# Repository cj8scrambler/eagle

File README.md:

Eagle Repository
=======

This is a repository to keep track of various hardware projects.

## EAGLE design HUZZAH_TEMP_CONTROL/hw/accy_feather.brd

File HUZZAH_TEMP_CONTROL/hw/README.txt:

To generate gerber files for OSH park:
  1) open schematic in Eagle
  2) Run the “CAM Processor”
  3) Select File -> CAM Processor
  4) Choose the OSHPark_eagle[version].cam that corresponds to your version of Eagle PCB
  5) Run 'Process Job'
  6) zip oshpark_gerbers.zip *.ger *.xln
  7) Upload oshpark_gerbers.zip to OSHPark

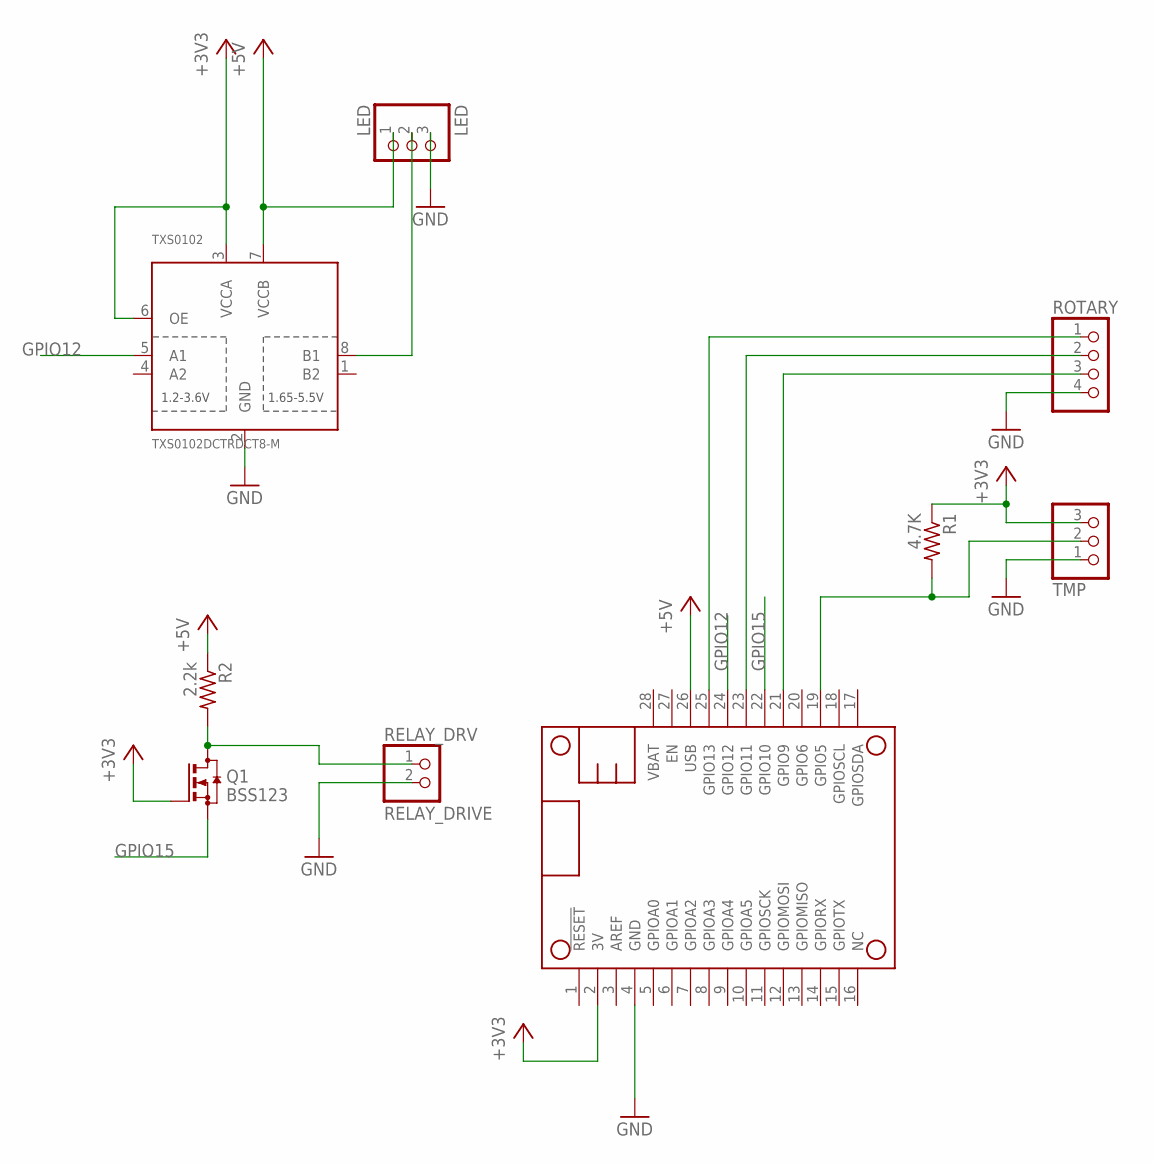
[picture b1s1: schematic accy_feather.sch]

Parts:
LED: LED; 1X03-CLEANBIG
MS1: FEATHERWING
Q1: BSS123; SOT23
R1: 4.7K; R0603
R2: 2.2k; R0603
RELAY_DRV: RELAY_DRIVE; 1X02
ROTARY: PINHD-1X4; 1X04
TMP: PINHD-1X3CB; 1X03-CLEANBIG
TXS0102: TXS0102DCTRDCT8-M; DCT8-M

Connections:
+3V3: MS1.2 (3V), Q1.1 (G), R1.1, TMP.3, TXS0102.3 (VCCA), TXS0102.6 (OE)
+5V: LED.1, MS1.26 (USB), R2.1, TXS0102.7 (VCCB)
BTN: MS1.21 (GPIO9), ROTARY.3
GND: LED.3, MS1.4 (GND), RELAY_DRV.2, ROTARY.4, TMP.1, TXS0102.2 (GND)
GPIO12: MS1.24 (GPIO12), TXS0102.5 (A1)
GPIO15: MS1.22 (GPIO10), Q1.2 (S)
LED_DATA: LED.2, TXS0102.8 (B1)
unnamed: Q1.3 (D), R2.2, RELAY_DRV.1
ROT1: MS1.25 (GPIO13), ROTARY.1
ROT2: MS1.23 (GPIO11), ROTARY.2
TMP_DATA: MS1.19 (GPIO5), R1.2, TMP.2

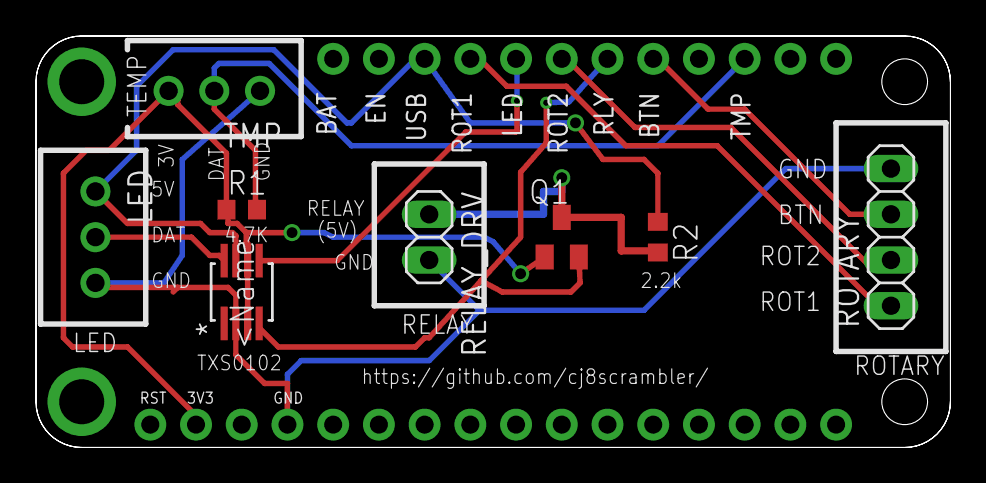
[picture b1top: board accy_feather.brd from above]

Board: 2 copper layers, 50.8 x 22.9 mm, 9 parts (0 on the bottom side), 11 nets.

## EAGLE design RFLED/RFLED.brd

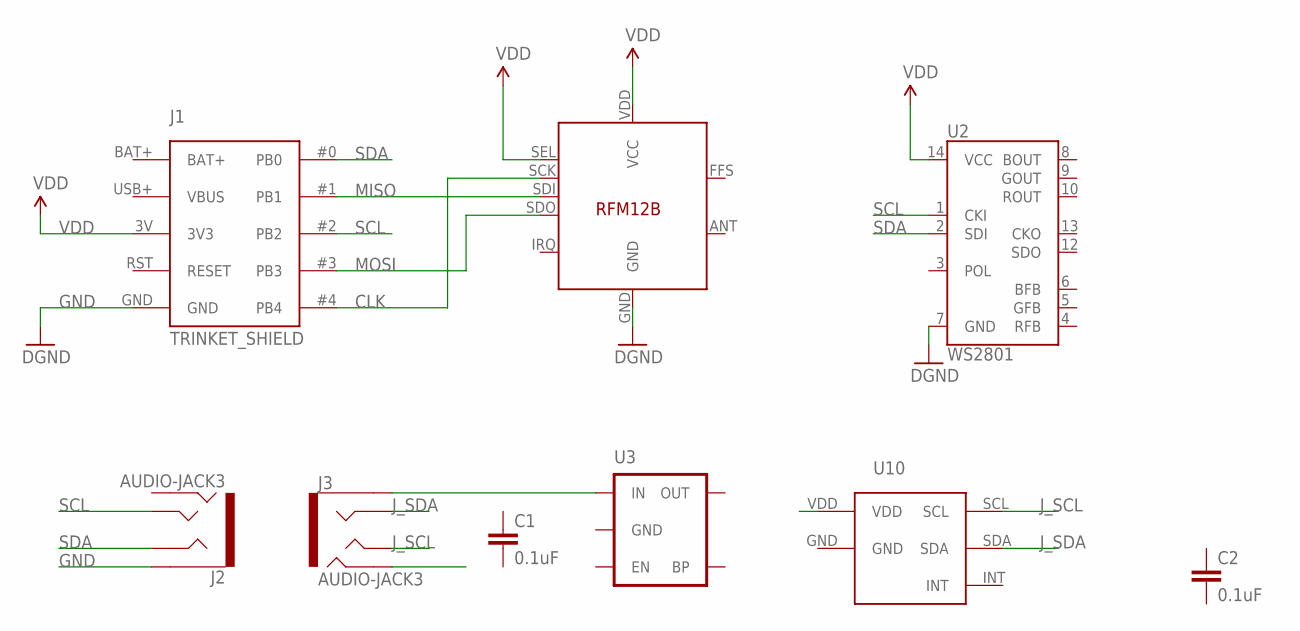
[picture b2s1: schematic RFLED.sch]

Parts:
C1, C2: 0.1uF; 0603-CAP
J1: TRINKET_SHIELD
J2, J3: AUDIO-JACK3; AUDIO-JACK-TRRS-SMD
U1: RFM12B
U2: WS2801; SOP-14
U3: MIC52053.3V; SOT23-5
U10: TC3472DFNL6_WIDE; DFNL6_WIDE

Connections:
BAT+: J1.BAT+
CLK: J1.#4 (PB4), U1.SCK
GND: J1.GND, J2.EARTH, U1.GND, U2.7 (GND)
J_SCL: J3.TIP, U10.SCL
J_SDA: J3.RING1, U10.SDA
J_VDD: J3.RING2
MISO: J1.#1 (PB1), U1.SDI
MOSI: J1.#3 (PB3), U1.SDO
unnamed: J3.EARTH, U3.1 (IN)
SCL: J1.#2 (PB2), J2.TIP, U2.1 (CKI)
SDA: J1.#0 (PB0), J2.RING1, U2.2 (SDI)
VBUS: J1.USB+ (VBUS)
VDD: J1.3V (3V3), U1.SEL, U1.VDD (VCC), U2.14 (VCC)

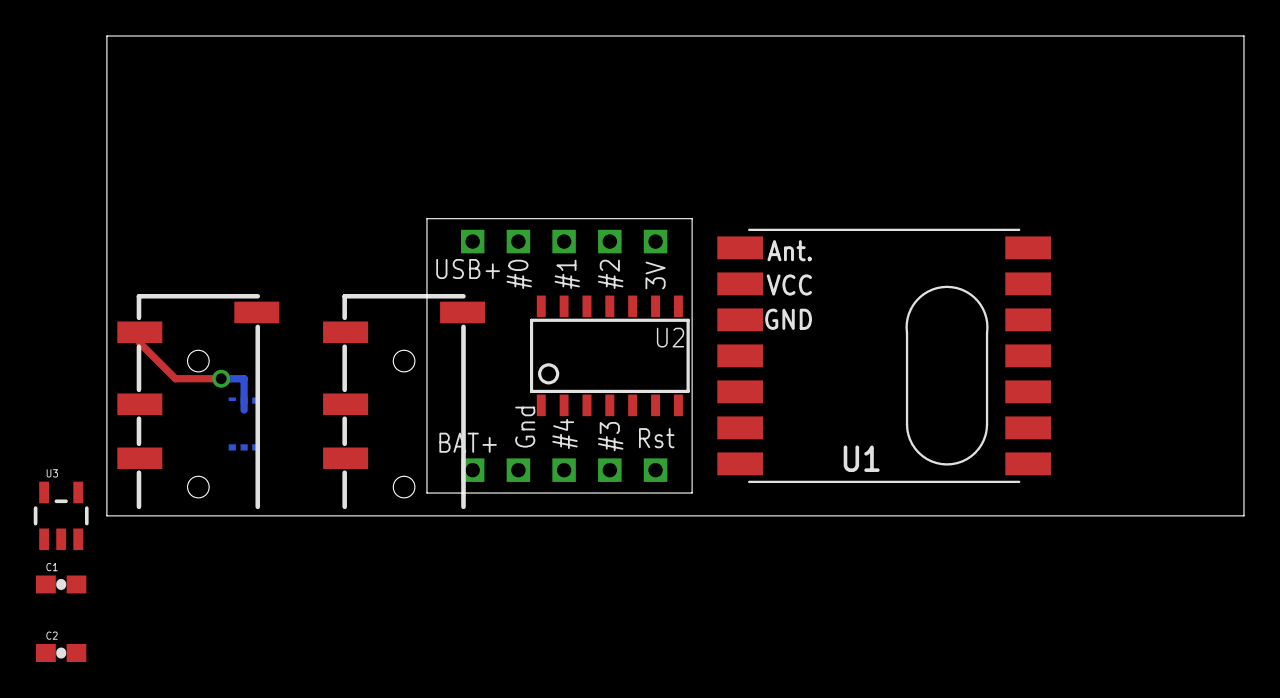
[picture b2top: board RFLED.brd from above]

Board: 2 copper layers, 63.2 x 26.7 mm, 9 parts (1 on the bottom side), 10 nets.

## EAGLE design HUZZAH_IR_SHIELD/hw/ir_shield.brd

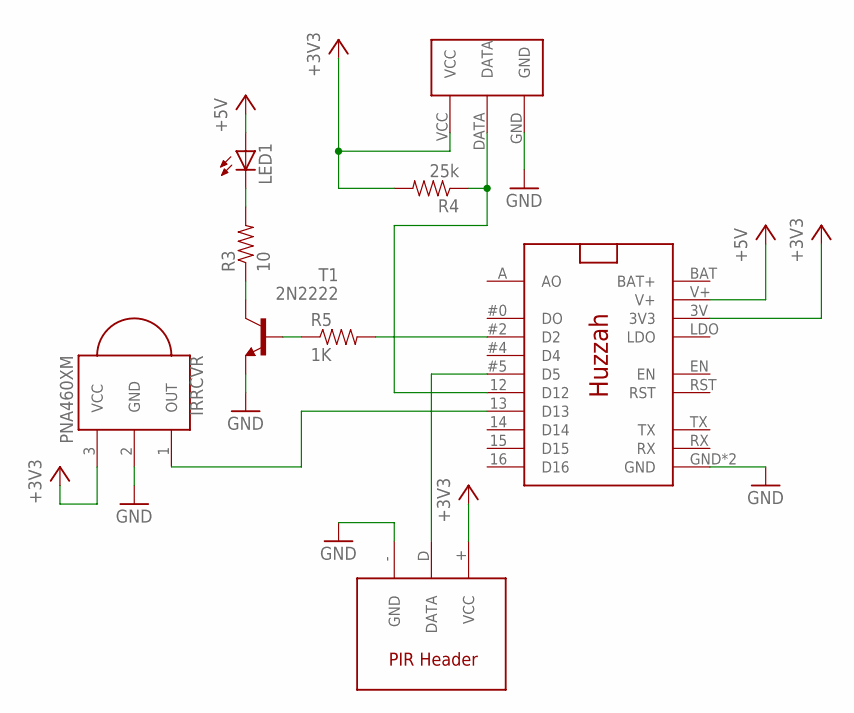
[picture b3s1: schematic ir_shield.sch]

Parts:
IRRCVR: PNA460XM
LED1: LEDIRL80A; IRL80A
R3: 10; 0402-RES
R4: 25k; 0402-RES
R5: 1K; 0402-RES
T1: 2N2222; TO92-EBC-OVAL
U$1: HUZZAH_SHIELDOUTSIDE; HUZZAH_OUTSIDE
U$3: DHT11VERT; DHT11-VERT
U$4: PIR; 3_PIN_HEADER

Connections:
+3V3: IRRCVR.3 (VCC), R4.2, U$1.3V (3V3), U$3.VCC, U$4.+ (VCC)
+5V: LED1.A, U$1.V+
GND: IRRCVR.2 (GND), T1.E, U$1.GND, U$1.GND2 (GND), U$3.GND, U$4.- (GND)
unnamed: LED1.K (C), R3.2
unnamed: R3.1, T1.C
unnamed: R5.1, T1.B
unnamed: R5.2, U$1.#2 (D2)
unnamed: IRRCVR.1 (OUT), U$1.13 (D13)
unnamed: R4.1, U$1.12 (D12), U$3.DATA
unnamed: U$1.#5 (D5), U$4.D (DATA)

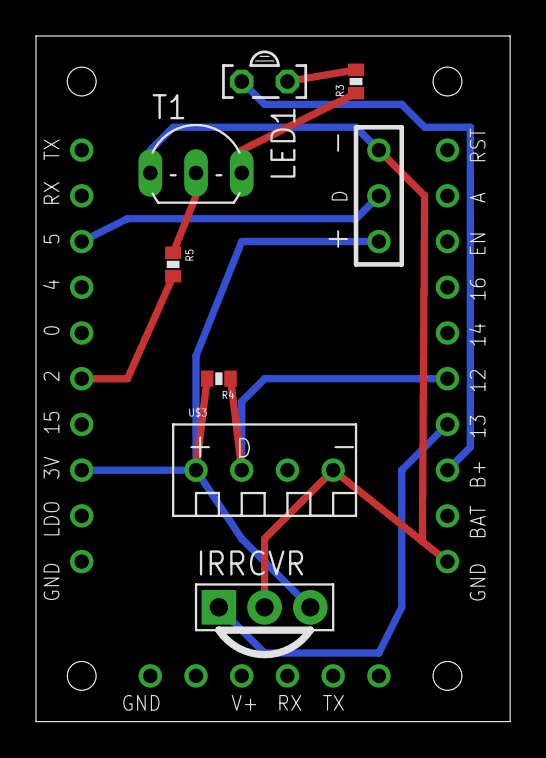
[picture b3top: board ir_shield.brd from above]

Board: 2 copper layers, 26.3 x 38.1 mm, 9 parts (0 on the bottom side), 10 nets.

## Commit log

2014-10-22 Setup initial project
    Check in library without much in it.
2014-10-22 Start on DFNL-6 packages for TCS3472
2014-10-23 Start on TCS3472
2014-10-23 Cleaned up some parts and started RFLED project
2014-10-23 More tedious updates.
2016-06-24 Huzzah IR blaster shield
    Shield for Adafruit Huzzah which adds IR transmitter, IR receiver
    and temp/humidity sensor. To be used for wifi based IR remote
    control of an air conditioner.
2016-06-24 Add a readme.
2016-06-27 Add initial source code
    Add initial Arduino source code used to verify the peripheral
    devices. Also re-arranged files into hw/sw directories.
2016-06-27 Added SSDP support
    Added Simple Service Discrover Protocol support for
    smartthings integration. Also moved into directory with
    matching parent name to make Arduino IDE happy.
2016-06-29 Add NeoPixel output
    Not really related to WiFi IR transmitter, but added neopixel output.
    Re-uses the IR LED pin.
2016-08-17 Initial Huzzah based temp controller
    Add a README with some general design principles and some
    basic code which compiles but hasn't been tested.
2016-08-17 HUZZAH temp: Add UI updates and data logging
    Add support for status LEDs and alphanum LED array. Remove the
    Wifi credentials UI template code.
    Also add NTP time sync and data logging.
2016-08-17 HUZZAH temp: Added relay control with hysteresis and compressor mode
    Added temperature hysterisis and compressor mode. Implemented relay control
    based on temperature readings. Updated UI to handle setting hysterisis and
    compressor mode.
2016-08-18 HUZZAH temp: refactor code
    Break code up int NTP/UI/main code blocks
2016-08-18 HUZZAH temp: refactor HTTP code
    Break HTTP code into seperate files. Add a basic form for viewing/changing
    the system parameters
2016-08-31 HUZZAH temp: Verfied alphanum output
    Verfied on actual hardware. Alphanumeric output is working.
    Moved all math to integer based.
2016-08-31 HUZZAH temp: Updated HTML interface
    Added simple FORM with current status and ability to change settings.
2016-08-31 HUZZAH temp: Fixes for button based alphanumeric UI
2016-11-18 Added MQTT logging
    Log data to MQTT broker. Also added support for a 2nd temp
    sensor (DS18B20) as an aux temp sensor.
2016-11-18 Update credentials.h for new paramaters
2016-11-30 Update HUZZAH temp documentation
2016-12-13 Remove support for TMP36/LM50
    Remove support for analog temp sensor because it's just not very
    accurate. The A/D on the ESP8266 only made it worse. Now there
    is support for 1 or 2 DS18B20 temp sensors.
    Also update documentation including some crude drawings of the
    hardware configuration.
2016-12-13 Fix inline images in README
2016-12-16 Add Custom Feather Board
    Created a custom feather board to make wiring up the accessory
    devices (scroll button, LEDs and temp sensors) easier.
    Available for order from OSHPark:
    https://oshpark.com/shared_projects/WBo4cvpj
2016-12-20 Update feather accy board to v1.1
    Added 4.7k pullup on temp data line
    Added level shifter on LED data line 3.3v->5V
2017-01-23 Update Temp Control README setup instructions
2017-02-07 Add TI TXS0102 part to my library
    Added TI TXS0102 2-Bit Bidirectional Voltage-Level Translator to
    library with larger SM8 package. Adafruit has a part in their
    library but it's the smaller VSSOP-8 package.
2017-02-07 Accessory board version 1.2
    Removed the MOSFET based level shifter for LED data and replaced
    it with a TI TXS01012. The MOSFET level shifter worked, but it
    wasn't fast enough to keep good data integrity for the WS2811 LED
    driver.
    I also routed the relay control through the same TXS01012 level
    shifter so it can be safely used to drive an external SSR instead
2017-02-07 Updated OSHPark design rules and gerber export CAM jobs
    Added the OSHPark design rule check file. It causes a lot of
    "Stop Mask" violations which I ignore.
    Updated the gerber export CAM job for Eagle 7.2+. Also added
    a README.txt so I can remember how to export the CAM files next
    time.
2017-02-24 Accessory board version 2.0
    Added a pulldown on the high voltage side of the relay output. This
    is needed because the level shifter can drive it high when it's floating
    which causes board instability.
    Added on-board 10A relay (Digi-Key Part #Z2763-ND) to the bottom side.
    There are 2 choices for relay control now:
    - You can place the "Relay Drive" header and wire an external relay
2017-02-25 Update README for v2.0 hardware
2017-02-25 Update inline image of accy board.
2017-03-09 Tested on assembled hardware: Various bugfixes
    MQTT re-connect needs to back off. If it loops too tight the
    board watchdogs.
    Only update EEPROM on settings change in idle mode. Otherwise
    every scroll caused EEPROM write slowing things down and wasting
    write cycles.
    LED mode should be RGB (not GRB).
2017-05-21 Accessory board version 2.1
    Moved relay to a transistor based 1-way level shifter. The
    2-way level shifter was causing problems with boot mode pins.
2017-05-21 Clean up temp sensor detection
    Temp sensor detection with multiple temp sensors wasn't reliable.
    Fixed some detection issues and added more debug prints.
2017-05-21 Update README for 2.1 board rev

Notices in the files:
parts and their libraries:
SparkFun-Passives: Licensing: Creative Commons ShareAlike 4.0 International - https://creativecommons.org/licenses/by-sa/4.0
COPYRIGHT: Copyright C 2015 Accelerated Designs. All rights reserved
